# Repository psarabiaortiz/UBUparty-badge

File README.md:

# UBUparty-badge
This repository contains the pcb badge done for the event UBUparty 2019.

The objective was to make a PCB badge compatible with Microbit Edge connector, hackeable and good looking.

The process to design the badge take a couple of days and its quite simple, just by uusing the KiCAD tool Bitmap to component converter, an image is set in the front and in the back a standard prototyping layout was set so any of the participants could design and implement its own circuit.

the back side pattern was obtained from here: https://github.com/rxseger/kicad-proto-pcb

The result was this:

Enjoy!

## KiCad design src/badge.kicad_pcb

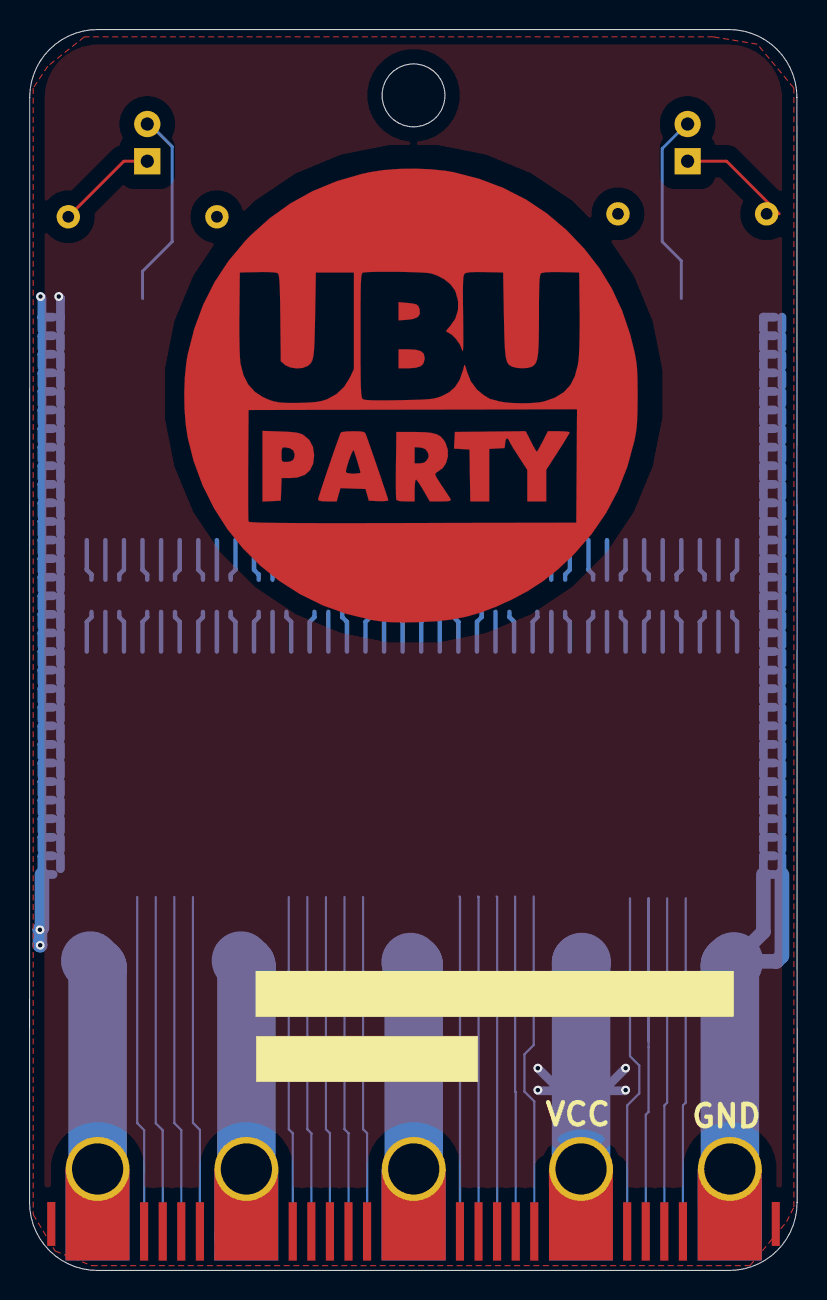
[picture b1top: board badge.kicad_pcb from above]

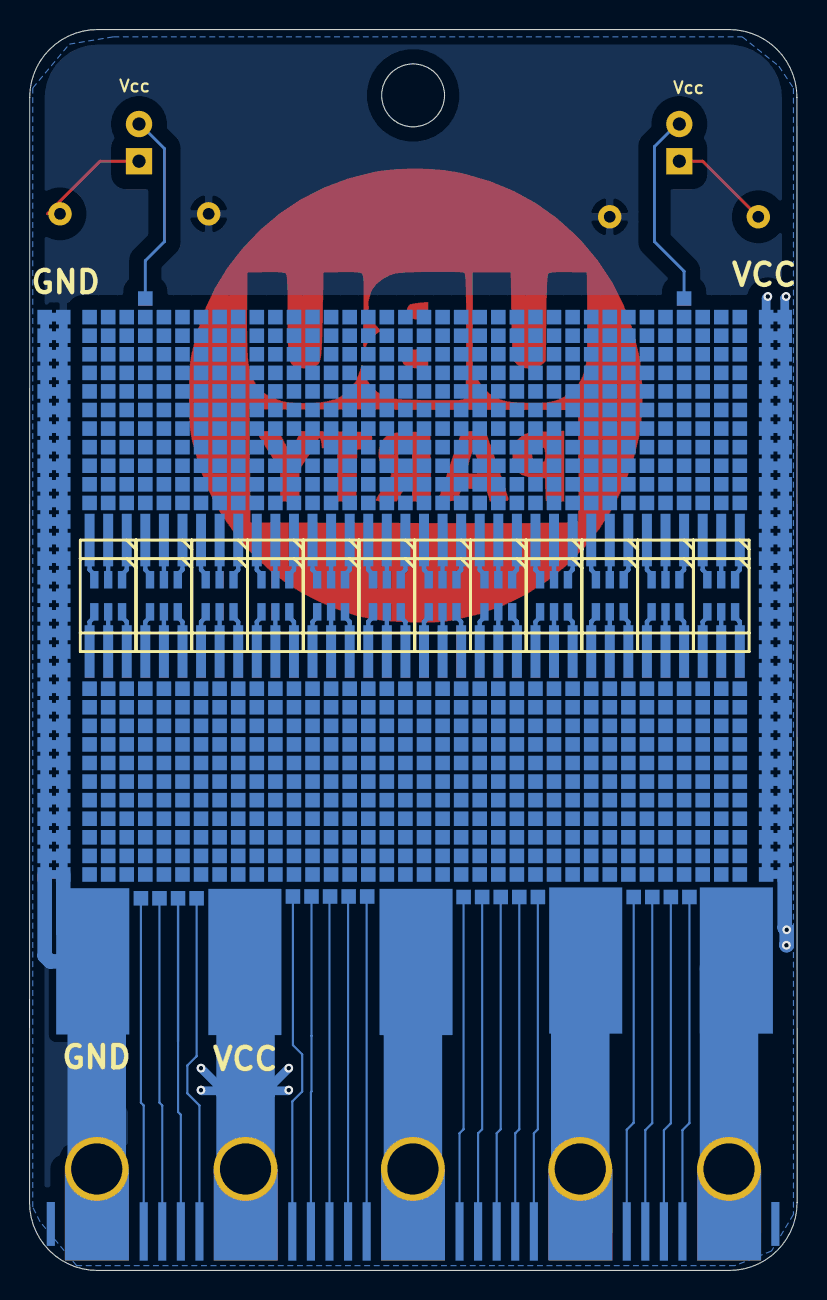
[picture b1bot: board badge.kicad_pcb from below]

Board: 2 copper layers, 52.5 x 84.8 mm, 965 parts (960 on the bottom side), 6 nets.

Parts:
D1, D2: LED; LED_D5.0mm
J1: Conn_01x25_Male; microbit_edge
R1, R2: R; R_Axial_DIN0207_L6.3mm_D2.5mm_P10.16mm_Horizontal
U1, U3, U5, U7, U9, U11, U13, U15, U17, U19, U21, U23: PROTO_SOIC6; proto_soic6
U2, U4, U6, U8, U10, U12, U14, U16, U18, U20, U22, U24: PROTO_SOT23; proto_sot23
U25, U26, U27, U28, U29, U30, U31, U32, U33, U34, U35, U36, U37, U38, U39, U40, U41, U42, U43, U44, U45, U46, U47, U48, U49, U50, U51, U52, U53, U54, U55, U56, U57, U58, U59, U60, U61, U62, U63, U64, U65, U66, U67, U68, U69, U70, U71, U72, U73, U74, U75, U76, U77, U78, U79, U80, U81, U82, U83, U84, U85, U86, U87, U88, U89, U90, U91, U92, U93, U94, U94#2, U94#3, U94#4, U94#5, U94#6, U94#7, U94#8, U94#9, U94#10, U94#11, U94#12, U94#13, U94#14, U94#15, U94#16, U94#17, U94#18, U94#19, U94#20, U94#21, U94#22, U94#23, U94#24, U94#25, U94#26, U94#27, U94#28, U94#29, U94#30, U94#31, U94#32, U94#33, U94#34, U94#35, U94#36, U94#37, U94#38, U94#39, U94#40, U94#41, U94#42, U94#43, U94#44, U94#45, U94#46, U94#47, U94#48, U94#49, U94#50, U94#51, U94#52, U94#53, U94#54, U94#55, U94#56, U94#57, U94#58, U94#59, U94#60, U94#61, U94#62, U94#63, U94#64, U94#65, U94#66, U94#67, U94#68, U94#69, U94#70, U94#71, U94#72, U94#73, U94#74, U94#75, U94#76, U94#77, U94#78, U94#79, U94#80, U94#81, U94#82, U94#83, U94#84, U94#85, U94#86, U94#87, U94#88, U94#89, U94#90, U94#91, U94#92, U94#93, U94#94, U94#95, U94#96, U94#97, U94#98, U94#99, U94#100, U94#101, U94#102, U94#103, U94#104, U94#105, U94#106, U94#107, U94#108, U94#109, U94#110, U94#111, U94#112, U94#113, U94#114, U94#115, U94#116, U94#117, U94#118, U94#119, U94#120, U94#121, U94#122, U94#123, U94#124, U94#125, U95, U96, U97, U98, U98#2, U98#3, U99, U100, U101, U102, U103, U104, U105, U106, U107, U108, U109, U110, U111, U112, U113, U114, U115, U116, U117, U118, U119, U120, U121, U122, U123, U124, U125, U126, U127, U128, U129, U130, U131, U132, U133, U134, U135, U136, U137, U138, U139, U140, U141, U141#2, U141#3, U141#4, U141#5, U141#6, U141#7, U141#8, U141#9, U141#10, U141#11, U141#12, U141#13, U141#14, U141#15, U141#16, U141#17, U141#18, U141#19, U142, U143, U144, U145, U146, U147, U148, U149, U150, U151, U152, U153, U154, U155, U156, U157, U158, U159, U160, U161, U162, U163, U164, U165, U166, U167, U168, U169, U170, U171, U172, U173, U174, U175, U176, U177, U178, U179, U181, U182, U183, U184, U185, U186, U187, U189, U190, U191, U192, U193, U194, U196, U197, U198, U199, U200, U201, U202, U203, U204, U206, U207, U208, U209, U210, U211, U212, U213, U215, U216, U217, U218, U219, U220, U222, U223, U225, U226, U227, U228, U229, U230, U231, U232, U233, U234, U235, U236, U237, U238, U239, U240, U241, U242, U243, U244, U245, U246, U247, U248, U249, U250, U251, U252, U253, U255, U256, U257, U258, U259, U262, U263, U264, U265, U266, U267, U268, U269, U270, U271, U273, U274, U275, U276, U277, U278, U279, U281, U282, U283, U284, U285, U286, U287, U288, U289, U290, U291, U292, U294, U295, U296, U297, U298, U299, U301, U302, U303, U304, U305, U306, U307, U308, U309, U310, U311, U312, U314, U315, U316, U317, U318, U319, U321, U322, U323, U324, U325, U326, U327, U328, U329, U331, U332, U333, U334, U335, U336, U337, U338, U339, U340, U341, U342, U343, U346, U347, U348, U349, U350, U351, U352, U353, U354, U355, U356, U357, U358, U359, U360, U361, U362, U364, U365, U366, U367, U368, U369, U370, U371, U372, U373, U374, U375, U376, U377, U378, U379, U380, U382, U383, U384, U385, U386, U387, U388, U389, U391, U392, U393, U394, U395, U396, U397, U398, U402, U403, U404, U405, U406, U407, U408, U409, U410, U411, U412, U413, U414, U415, U416, U417, U418, U419, U420, U421, U424, U425, U426, U427, U428, U429, U430, U431, U432, U433, U434, U435, U436, U437, U438, U439, U440, U441, U442, U443, U444, U445, U446, U447, U448, U449, U450, U451, U452, U453, U454, U455, U456, U457, U458, U459, U460, U461, U462, U463, U465, U466, U467, U469, U470, U471, U472, U473, U474, U475, U476, U477, U478, U479, U480, U481, U482, U483, U484, U485, U486, U487, U488, U489, U490, U491, U492, U494, U496, U497, U498, U499, U500, U501, U503, U504, U505, U506, U507, U508, U509, U511, U512, U513, U517, U518, U519, U520, U521, U522, U523, U524, U525, U526, U527, U528, U529, U530, U531, U532, U533, U534, U535, U536, U537, U538, U539, U540, U541, U542, U543, U544, U545, U546, U547, U548, U549, U550, U551, U552, U553, U554, U555, U556, U561, U562, U563, U564, U565, U566, U567, U568, U569, U570, U571, U572, U573, U595, U596, U597, U598, U599, U600, U601, U602, U603, U604, U605, U606, U607, U608, U609, U610, U611, U612, U613, U614, U615, U616, U617, U618, U619, U620, U621, U622, U623, U624, U625, U629, U630, U631, U632, U633, U634, U637, U638, U639, U640, U641, U642, U643, U644, U645, U650, U651, U658, U659, U660, U661, U662, U663, U666, U667, U668, U671, U679, U680, U681, U682, U683, U684, U685, U686, U687, U688, U689, U690, U691, U692, U693, U694, U695, U696, U697, U698, U699, U700, U701, U702, U703, U704, U705, U706, U707, U708, U709, U710, U711, U712, U713, U714, U715, U716, U717, U718, U719, U720, U721, U722, U723, U724, U725, U726, U727, U729, U730, U731, U734, U735, U739, U740, U741, U742, U747, U748, U749, U750, U752, U753, U754, U755, U763, U764, U765, U766, U767, U768, U769, U777, U778, U779, U780, U781, U782, U783, U785, U786, U794, U795, U796, U797, U798, U799, U800, U801, U802, U803, U804, U805, U806, U811, U812, U813, U814, U815, U816, U817, U818, U819, U820, U821, U822, U823, U828, U829, U830, U831, U832, U833, U834, U839, U840, U841, U842, U843, U844, U845, U846, U847, U848, U853, U854, U855, U856, U857, U859, U860, U864, U865, U866, U867, U868, U869, U870, U871, U872, U877, U878, U879, U880, U881, U882, U887, U888, U889, U890, U891, U892, U893, U894, U895, U896, U897, U902, U903, U904, U905, U906, U907, U908, U909, U910, U911, U912, U913, U914, U915, U916, U917, U918, U919, U920, U921, U922, U923, U924, U925, U936, U937, U938, U939, U940, U941, U942, U955, U956, U957, U958, U959, U960, U961, U965, U966, U967, U968, U969, U970, U971, U972, U973, U974, U975, U979, U980, U981, U982, U983, U984, U985, U986, U987, U988, U989, U990, U991, U992, U993, U994, U997, U1001: PAD; proto_pad

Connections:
+3V3: J1.4, U94#63.1, U94#64.1, U94#65.1, U94#66.1, U94#67.1, U94#68.1, U94#69.1, U94#70.1, U94#71.1, U94#72.1, U94#73.1, U94#74.1, U94#75.1, U94#76.1, U94#77.1, U94#78.1, U94#79.1, U94#80.1, U94#81.1, U94#82.1, U94#83.1, U94#84.1, U94#85.1, U94#86.1, U94#87.1, U94#88.1, U94#89.1, U94#90.1, U94#91.1, U94#92.1, U94#93.1, U94#94.1, U94#95.1, U94#96.1, U94#97.1, U94#98.1, U94#99.1, U94#100.1, U94#101.1, U94#102.1, U94#103.1, U94#104.1, U94#105.1, U94#106.1, U94#107.1, U94#108.1, U94#109.1, U94#110.1, U94#111.1, U94#112.1, U94#113.1, U94#114.1, U94#115.1, U94#116.1, U94#117.1, U94#118.1, U94#119.1, U94#120.1, U94#121.1, U94#122.1, U94#123.1, U94#124.1
GND: J1.5, R1.2, R2.2, U94.1, U94#2.1, U94#3.1, U94#4.1, U94#5.1, U94#6.1, U94#7.1, U94#8.1, U94#9.1, U94#10.1, U94#11.1, U94#12.1, U94#13.1, U94#14.1, U94#15.1, U94#16.1, U94#17.1, U94#18.1, U94#19.1, U94#20.1, U94#21.1, U94#22.1, U94#23.1, U94#24.1, U94#25.1, U94#26.1, U94#27.1, U94#28.1, U94#29.1, U94#30.1, U94#31.1, U94#32.1, U94#33.1, U94#34.1, U94#35.1, U94#36.1, U94#37.1, U94#38.1, U94#39.1, U94#40.1, U94#41.1, U94#42.1, U94#43.1, U94#44.1, U94#45.1, U94#46.1, U94#47.1, U94#48.1, U94#49.1, U94#50.1, U94#51.1, U94#52.1, U94#53.1, U94#54.1, U94#55.1, U94#56.1, U94#57.1, U94#58.1, U94#59.1, U94#60.1, U94#61.1, U94#62.1
unnamed: D1.1, R1.1
unnamed: D1.2, U98.1
unnamed: D2.1, R2.1
unnamed: D2.2, U98#2.1

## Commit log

2019-10-22 Update Readme.md
    Added images
2019-10-22 Update Readme.md
    Sources porovided
2019-10-22 Initial commit
    This a second revision of the badge that contains all working connections.
2024-07-20 Modified gitignore
2025-08-21 Added Version 24 and 25 of the badge
